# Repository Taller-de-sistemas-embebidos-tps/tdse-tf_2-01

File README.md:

# Sistema de detección de apneas y variaciones de oxigenación durante el sueño
<div align="center">

Trabajo Final - Taller de Sistemas Embebidos - FIUBA

|Alumno|Padron|
|------|-------|
|Tomás Musso Carboni|111548|
|Santiago Archetti|110707|
|Alan Romero|108316|
</div>

### Entrega
Se establece el plazo para entregar el proyecto finalizado para el periodo febrero-marzo.

## 1.1 Justificación de la elección del proyecto
Este proyecto se eligió porque los problemas respiratorios durante el sueño, como la apnea<sup>[1]</sup>, son muy comunes y muchas veces no se detectan a tiempo. La falta de diagnóstico puede generar cansancio crónico, bajo rendimiento y riesgos cardiovasculares, pero los estudios clínicos tradicionales suelen ser costosos y difíciles de realizar en el hogar. Por eso, un dispositivo portátil que mida la respiración y la saturación de oxígeno durante la noche resulta una herramienta útil y accesible para identificar posibles alteraciones.
Desde el punto de vista tecnológico, el proyecto es adecuado para el área de sistemas embebidos porque integra sensores reales, procesamiento digital, comunicación inalámbrica y manejo de bajo consumo. Además, el hardware seleccionado (MAX30102 y STM32F103RB) es económico, fácil de conseguir y cuenta con buena documentación, lo que facilita el desarrollo y permite enfocarse en el funcionamiento del sistema sin una complejidad excesiva. En conjunto, esto hace que el proyecto sea realizable, educativo y al mismo tiempo relevante desde lo biomédico.
Para la elección del proyecto, se realiza un análisis profundo de los distintos criterios que lo componen, asignando un peso a cada uno de ellos para luego hacer un análisis total.
|Criterio|Descripción|Puntuación|Peso final|
|----------|-------------|------------|------------|
|Tiempo y facilidad de implementación. Peso (7) |El uso del sensor MAX30102 y el microcontrolador STM32F103RB presenta una complejidad moderada, debido a la necesidad de configurar correctamente la comunicación I²C, filtrar la señal PPG y aplicar algoritmos de cálculo de SpO₂ y frecuencia respiratoria. Sin embargo, existe amplia documentación y librerías disponibles, lo que reduce las dificultades de implementación. En conjunto, se considera que la complejidad técnica es manejable dentro del marco de un proyecto de sistemas embebidos.| <p align="center">7</p> | 49 |
|Disponibilidad y costo de hardware. Peso (8) | Los componentes principales —sensor óptico MAX30102, microcontrolador STM32, módulo Bluetooth y un buzzer/LED para alarmas— son económicos, fáciles de conseguir y ampliamente utilizados en proyectos biomédicos educativos. Esto permite realizar pruebas sin un costo elevado y garantiza buena disponibilidad de reemplazos. |<p align="center">9</p>|72|
|Facilidad de realización de pruebas. Peso (5)|La verificación del funcionamiento del sistema puede realizarse mediante lectura directa de las señales PPG, monitoreo en tiempo real por UART/Bluetooth y observación de la activación de alarmas locales. Además, se pueden usar herramientas básicas como un multímetro o un osciloscopio para validar etapas eléctricas, lo que facilita enormemente el proceso de pruebas y depuración.| <p align="center">7</p>| 35 |
|Utilidad e interés personal en el proyecto. Peso (9)| El proyecto presenta un alto interés personal debido a su relación con aplicaciones biomédicas reales, la posibilidad de detectar apneas y desaturaciones durante el sueño, y su potencial mejora en versiones futuras. Además, permite aplicar conocimientos de sensores ópticos, filtrado digital y diseño embebido, lo que resulta atractivo tanto desde el punto de vista académico como práctico.|<p align="center"> 9</p>| 81 |

<p align="center"><b>Tabla 1: Evaluación de criterios del proyecto</b></p>

## 2.1 Objetivo del Proyecto
Diseñar y desarrollar un dispositivo portátil no invasivo capaz de medir en tiempo real la saturación de oxígeno (SpO₂) y la frecuencia respiratoria mediante técnicas de fotopletismografía. El objetivo es obtener señales fisiológicas confiables, procesarlas de forma local a través del microcontrolador STM32F103RB y generar alertas inmediatas ante condiciones anómalas, garantizando un monitoreo continuo y seguro

## 2.2 Propósito del Proyecto
El propósito es brindar una herramienta accesible y de bajo consumo para el seguimiento básico de parámetros respiratorios y de oxigenación, destinada a aplicaciones clínicas simples, monitoreo domiciliario y apoyo en la detección temprana de eventos como apnea o desaturación. Se busca complementar el trabajo de profesionales de la salud y ofrecer al usuario información clara y oportuna sobre su estado fisiológico.

## 2.3 Alcance del Proyecto
El proyecto abarca el diseño electrónico, la implementación del firmware y el procesamiento digital de la señal proveniente del sensor MAX30102 para la obtención de SpO₂ y frecuencia respiratoria. Incluye la integración de alarmas locales (buzzer/LED) configuradas por umbrales, así como la transmisión inalámbrica de datos mediante Bluetooth hacia una aplicación móvil. El alcance no contempla funciones diagnósticas avanzadas ni interpretación médica, limitándose al monitoreo y notificación de parámetros básicos.
Se establece la primer mesa de feberero como fecha para finalizar el proyecto.

## 3.1 Arquitectura del sistema
El diseño se estructura en cuatro bloques funcionales: 
1.	Adquisición: captura de la señal de flujo sanguíneo del dedo<sup>[2]</sup> del paciente mediante fotodiodos y LEDs (Rojo/IR). 
2.	Procesamiento: filtrado digital y cálculo de algoritmos en el microcontrolador. 
3.	Interfaz: indicadores visuales y sonoros para el usuario. 
4.	Comunicación: transmisión inalámbrica de telemetría y almacenamiento de parámetros. 

## 3.2 Diseño de Hardware
-	Sensor MAX30102: módulo integrado de oximetría y ritmo cardíaco. Se comunica vía I²C y opera a 3,3V. Provee las lecturas crudas de absorción de luz roja e infrarroja necesarias para calcular la saturación y derivar la respiración. 
-	Microcontrolador STM32F103RB: seleccionado por su núcleo ARM Cortex-M4F (con unidad de punto flotante), esencial para ejecutar filtros digitales eficientes. Gestiona los buses I²C (sensor, EEPROM) y UART (Bluetooth). 
-	Módulo Bluetooth HM-10: interfaz UART transparente para enviar datos seriales a dispositivos móviles (Smartphone/PC). 
-	Almacenamiento: memoria EEPROM externa (serie 24C0x) para guardar configuraciones de usuario, como umbrales de alarma o logs de eventos. 
-	Gestión de Energía: alimentación mediante batería Li-ion con regulación LDO a 3,3V. Implementa modos de bajo consumo (STOP) durante la inactividad. 

## 3.3 Procesamiento de la señal
El firmware, desarrollado en C con librerías HAL, ejecuta el siguiente flujo cíclico: 
1.	Adquisición de Datos: lectura de la FIFO del MAX30102 para obtener muestras de los canales Rojo e Infrarrojo (IR). 
2.	Pre-procesamiento: aplicación de un filtro para eliminar el componente de continua (DC) y ruido de alta frecuencia.<sup>[3]</sup> 
3.	Cálculo de SpO₂: se basa en la relación de ratios ($R$) entre las componentes AC y DC de ambas longitudes de onda<sup>[4]</sup>:
    
$$ R = \frac{AC_{red}\cdot AC_{ir}}{DC_{red} \cdot Dc_{ir}} $$

$$ SpO_2 = 110 - 25 \cdot R $$

4.	Estimación de Frecuencia Respiratoria: se realiza mediante el análisis de la variabilidad de la línea base o la modulación de amplitud (envolvente) de la señal PPG, extrayendo componentes de baja frecuencia (0,2 – 0,3 Hz). 
5.	Lógica de Control: si el SpO₂ cae por debajo del 90%, o si hay variaciones de la freuencia respiratoria, se activa el led indicador. Si se detecta apena se activa la alarma. Finalmente, se empaquetan los datos y se envían por UART. 

# 4.1 Requerimientos funcionales

| Grupo  | ID   | Requerimiento Funcional    | Descripción                                                                   |
|---|------|-----------------------------|-------------------------------------------------------------------------------|
|Adquisición | 1.1  | Adquisición de señales     | Capturar señales ópticas Rojo/IR del MAX30102 vía I²C.                        |
|   | 1.2  | Lectura periódica          | Obtener muestras desde la FIFO del sensor.                                    |
|   | 1.3  | Análisis de variación      | Detectar variaciones necesarias para SpO₂ y respiración.                      |
| Procesamiento  | 2.1  | Filtrado digital           | Aplicar filtrado.                                                             |
|   | 2.2  | Cálculo de SpO₂            | Calcular SpO₂ mediante el ratio R (AC/DC Rojo y AC/DC IR).                    |
|   | 2.3  | Cálculo de respiración     | Estimar frecuencia respiratoria mediante análisis de envolvente o línea base. |
|   | 2.4  | Empaquetado de datos       | Generar paquete con SpO₂, respiración y estado.                               |
|  Indicadores | 3.1  | Alarma crítica             | Activar alarma sonora cuando se detecta apnea.                                   |
|   | 3.2  | Indicadores LED            | Mostrar estados (crítico, normal, error) mediante LEDs.                       |
|  Comunicación | 4.1  | Comunicación Bluetooth     | Transmitir datos vía HM-10 por UART.                                          |
|   | 4.2  | Envío de parámetros        | Enviar SpO₂, respiraciones y estado del paciente a la app.                    |
|   | 4.3  | Registro de eventos        | Informar alarmas, desconexiones o estados especiales.                         |
|   | 4.4  | Recepción de configuración | Recibir umbrales y parámetros desde la aplicación.                            |
|  Memoria | 5.1  | Guardar configuración      | Almacenar umbrales y parámetros en EEPROM.                                    |
|   | 5.2  | Restaurar valores          | Recuperar valores predeterminados si hay error de memoria.                    |
| Alimentación  | 6.1  | Alimentación               | Funcionamiento con batería Li-Ion y regulación a 3.3V.                        |
|   | 6.2  | Bajo consumo               | Entrar en modo STOP cuando no hay actividad.                                  |
|   | 6.3  | Reactivación               | Retomar actividad ante movimiento o comando.                                  |
<p align="center"><b>Tabla 2: Requerimentos funcionales</b></p>

## 4.2 Diagrama de bloques
En la siguiente figura se dennota el diagrama de bloques funcional del proyecto.

<div align="center">
  
  <p><b>Figura 1. Diagrama de bloques</b></p>
</div>

## 5.1 Modos de uso

| **Modo** | **Descripción** | **Cotas / Umbrales** | **Comportamiento Especial** |
|---------|-----------------|----------------------|------------------------------|
| **Adulto** | Modo estándar para usuarios adultos. Utiliza configuraciones típicas de umbral para SpO₂ y respiración. | • SpO₂ crítico: < **90%**  <br>• Frecuencia respiratoria: rangos normales adulto | • Activa alarmas ante valores críticos. <br>• Envío de datos por Bluetooth. |
| **Niño** | Modo adaptado para usuarios pediátricos, con umbrales más sensibles. | • SpO₂ crítico: < **92–93%**  <br>• Frecuencia respiratoria: rangos normales niño | • Mayor sensibilidad a variaciones pequeñas. <br>• Alarmas ajustadas a parámetros pediátricos. |
| **Sleep (Bajo Consumo)** | Modo de ahorro energético para monitoreo prolongado nocturno. | • Mantiene umbrales según modo Adulto/Niño seleccionado. | • Reduce frecuencia de muestreo y procesamiento. <br>• **Si pasan más de 10 minutos sin lectura válida, el sistema se apaga automáticamente.** |
<p align="center"><b>Tabla 3: Modos de uso</b></p>

## Referencias
1. National Institutes of Health (NIH) – Sleep Apnea Fact Sheet. Disponible en https://www.nhlbi.nih.gov/health/sleep-apnea
2. Sally K. Longmore et al., “A Comparison of Reflective Photoplethysmography for Detection of Heart Rate, Blood Oxygen Saturation, and Respiration Rate at Various Anatomical Locations”, *Sensors*, vol. 19, no. 8, 1874, Apr. 2019. Disponible en: https://www.mdpi.com/1424-8220/19/8/1874
3.  Park J., Seok H. S., Kim S. S., & Shin H. (2022). *Photoplethysmogram Analysis and Applications: An Integrative Review*. Frontiers in Physiology, 12, Article 808451. doi:10.3389/fphys.2021.808451. Disponible en: https://www.ncbi.nlm.nih.gov/pmc/articles/PMC8920970/ 
4.  MAX30102 – Pulse Oximeter and Heart-Rate Sensor Datasheet. Maxim Integrated. https://datasheets.maximintegrated.com/en/ds/MAX30102.pdf

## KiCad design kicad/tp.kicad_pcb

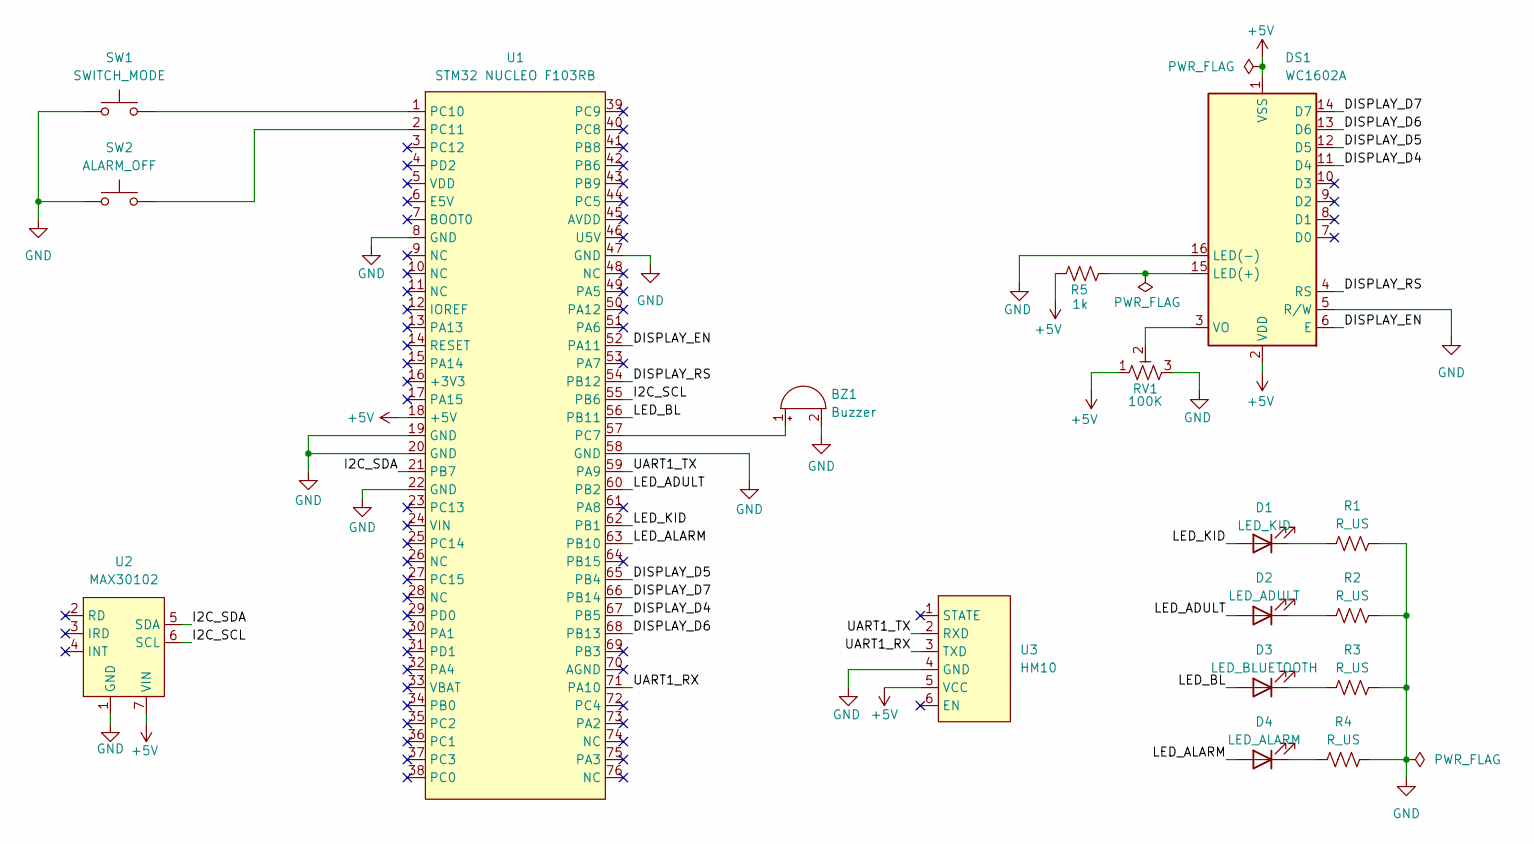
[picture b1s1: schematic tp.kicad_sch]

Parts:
BZ1: Buzzer; Buzzer_12x9.5RM7.6
D1: LED_KID; LED_D5.0mm
D2: LED_ADULT; LED_D5.0mm
D3: LED_BLUETOOTH; LED_D5.0mm
D4: LED_ALARM; LED_D5.0mm
DS1: WC1602A
R1, R2, R3, R4: R_US; R_Axial_DIN0207_L6.3mm_D2.5mm_P7.62mm_Horizontal
R5: 1k; R_Axial_DIN0207_L6.3mm_D2.5mm_P7.62mm_Horizontal
RV1: 100K; Potentiometer_Alps_RK163_Single_Horizontal
SW1: SWITCH_MODE; SW_PUSH-12mm_Wuerth-430476085716
SW2: ALARM_OFF; SW_PUSH-12mm_Wuerth-430476085716
U1: STM32 NUCLEO F103RB; NUCLEO F103RB
U2: MAX30102; PinHeader_1x07_P2.54mm_Vertical
U3: HM10; PinSocket_1x06_P2.54mm_Vertical

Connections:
+5V: DS1.1 (VSS), DS1.2 (VDD), R5.2, RV1.1, U1.18 (+5V), U2.7 (VIN), U3.5 (VCC)
/DISPLAY_D4: DS1.11 (D4), U1.67 (PB5)
/DISPLAY_D5: DS1.12 (D5), U1.65 (PB4)
/DISPLAY_D6: DS1.13 (D6), U1.68 (PB13)
/DISPLAY_D7: DS1.14 (D7), U1.66 (PB14)
/DISPLAY_EN: DS1.6 (E), U1.52 (PA11)
/DISPLAY_RS: DS1.4 (RS), U1.54 (PB12)
/I2C_SCL: U1.55 (PB6), U2.6 (SCL)
/I2C_SDA: U1.21 (PB7), U2.5 (SDA)
/LED_ADULT: D2.2 (A), U1.60 (PB2)
/LED_ALARM: D4.2 (A), U1.63 (PB10)
/LED_BL: D3.2 (A), U1.56 (PB11)
/LED_KID: D1.2 (A), U1.62 (PB1)
/UART1_RX: U1.71 (PA10), U3.3 (TXD)
/UART1_TX: U1.59 (PA9), U3.2 (RXD)
GND: BZ1.2 (-), DS1.5 (R/W), DS1.16 (LED(-)), R1.2, R2.2, R3.2, R4.2, RV1.3, SW1.1, SW2.1, U1.8 (GND), U1.19 (GND), U1.20 (GND), U1.22 (GND), U1.47 (GND), U1.58 (GND), U2.1 (GND), U3.4 (GND)
unnamed: BZ1.1 (+), U1.57 (PC7)
unnamed: D1.1 (K), R1.1
unnamed: D2.1 (K), R2.1
unnamed: D3.1 (K), R3.1
unnamed: D4.1 (K), R4.1
unnamed: DS1.15 (LED(+)), R5.1
unnamed: DS1.3 (VO), RV1.2
unnamed: SW1.2, U1.1 (PC10)
unnamed: SW2.2, U1.2 (PC11)

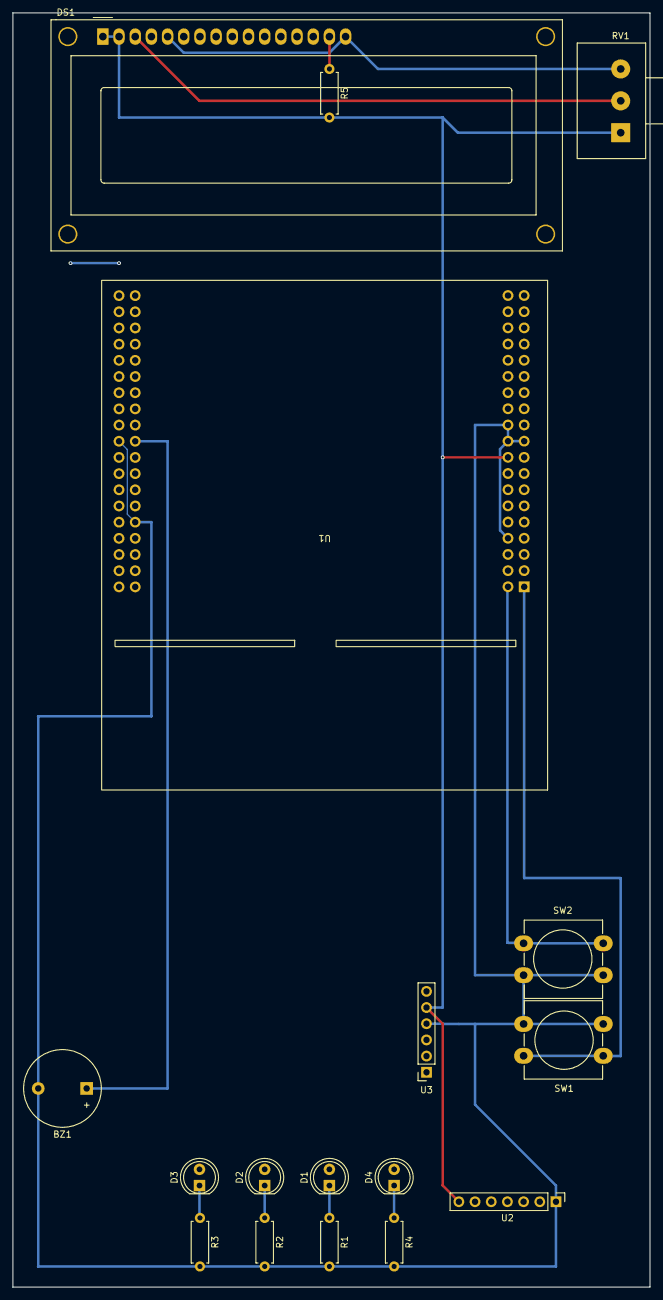
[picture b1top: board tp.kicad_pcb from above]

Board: 10 copper layers, 100.0 x 200.0 mm, 17 parts (0 on the bottom side), 25 nets.

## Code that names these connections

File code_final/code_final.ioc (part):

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Mcu.Name=STM32F103R(8-B)Tx
Mcu.Package=LQFP64
Mcu.UserName=STM32F103RBTx
PA10.Mode=Asynchronous
PA10.Signal=USART1_RX
PA11.GPIOParameters=GPIO_Label
PA11.GPIO_Label=DISPLAY_EN
PA11.Signal=GPIO_Output
PA13.GPIOParameters=GPIO_Label
PA13.GPIO_Label=TMS
PA13.Mode=Serial_Wire
PA13.Signal=SYS_JTMS-SWDIO
PA14.GPIOParameters=GPIO_Label
PA14.GPIO_Label=TCK
PA14.Mode=Serial_Wire
PA14.Signal=SYS_JTCK-SWCLK
PA2.GPIOParameters=GPIO_Speed,GPIO_PuPd,GPIO_Label,GPIO_Mode
PA2.GPIO_Label=USART_TX
PA2.GPIO_Mode=GPIO_MODE_AF_PP
PA2.GPIO_PuPd=GPIO_NOPULL
PA2.GPIO_Speed=GPIO_SPEED_FREQ_LOW
PA2.Mode=Asynchronous
PA2.Signal=USART2_TX
PA3.GPIOParameters=GPIO_Speed,GPIO_PuPd,GPIO_Label,GPIO_Mode
PA3.GPIO_Label=USART_RX
PA3.GPIO_Mode=GPIO_MODE_AF_PP
PA3.GPIO_PuPd=GPIO_NOPULL
PA3.GPIO_Speed=GPIO_SPEED_FREQ_LOW
PA3.Mode=Asynchronous
PA3.Signal=USART2_RX
PA5.GPIOParameters=GPIO_Speed,GPIO_PuPd,GPIO_Label,GPIO_ModeDefaultOutputPP
PA5.GPIO_Label=LD2 [Green Led]
PA5.GPIO_ModeDefaultOutputPP=GPIO_MODE_OUTPUT_PP
PA5.GPIO_PuPd=GPIO_NOPULL
PA5.GPIO_Speed=GPIO_SPEED_FREQ_LOW
PA5.Signal=GPIO_Output
PA9.Mode=Asynchronous
PA9.Signal=USART1_TX
PB1.GPIOParameters=GPIO_Label
PB1.GPIO_Label=LED_KID
PB1.Signal=GPIO_Output
PB10.GPIOParameters=GPIO_Label
PB10.GPIO_Label=LED_ALARM
PB10.Signal=GPIO_Output
PB11.GPIOParameters=GPIO_Label
PB11.GPIO_Label=LED_BL
PB11.Signal=GPIO_Output
PB12.GPIOParameters=GPIO_Label
PB12.GPIO_Label=DISPLAY_RS
PB12.Signal=GPIO_Output
PB13.GPIOParameters=GPIO_Label
PB13.GPIO_Label=DISPLAY_D6
PB13.Signal=GPIO_Output
PB14.GPIOParameters=GPIO_Label
PB14.GPIO_Label=DISPLAY_D7
PB14.Signal=GPIO_Output
PB2.GPIOParameters=GPIO_Label
PB2.GPIO_Label=LED_ADULT
PB2.Signal=GPIO_Output
PB3.GPIOParameters=GPIO_Label
PB3.GPIO_Label=SWO
PB3.Signal=SYS_JTDO-TRACESWO
PB4.GPIOParameters=GPIO_Label
PB4.GPIO_Label=DISPLAY_D5
PB4.Signal=GPIO_Output
PB5.GPIOParameters=GPIO_Label
PB5.GPIO_Label=DISPLAY_D4
PB5.Signal=GPIO_Output
PB6.Mode=I2C
PB6.Signal=I2C1_SCL
PB7.Mode=I2C
PB7.Signal=I2C1_SDA
PC10.GPIOParameters=GPIO_PuPd,GPIO_Label
PC10.GPIO_Label=BTN_MODE
PC10.GPIO_PuPd=GPIO_PULLUP
PC10.Signal=GPIO_Input
PC11.GPIOParameters=GPIO_PuPd,GPIO_Label
PC11.GPIO_Label=BTN_ALARM
PC11.GPIO_PuPd=GPIO_PULLUP
PC11.Signal=GPIO_Input
PC12.GPIOParameters=GPIO_PuPd,GPIO_Label
PC12.GPIO_Label=BTN_PAIRING
PC12.GPIO_PuPd=GPIO_NOPULL
PC12.Signal=GPIO_Input
PC13-TAMPER-RTC.GPIOParameters=GPIO_PuPd,GPIO_Label
PC13-TAMPER-RTC.GPIO_Label=B1 [Blue PushButton]
PC13-TAMPER-RTC.GPIO_PuPd=GPIO_NOPULL
PC13-TAMPER-RTC.Signal=GPXTI13
PC14-OSC32_IN.Mode=LSE-External-Oscillator
PC14-OSC32_IN.Signal=RCC_OSC32_IN
PC15-OSC32_OUT.Mode=LSE-External-Oscillator
PC15-OSC32_OUT.Signal=RCC_OSC32_OUT
PC7.GPIOParameters=GPIO_Label
PC7.GPIO_Label=BUZZER
PC7.Signal=GPIO_Output
PD0-OSC_IN.Mode=HSE-External-Clock-Source
PD0-OSC_IN.Signal=RCC_OSC_IN
PD1-OSC_OUT.Mode=HSE-External-Clock-Source
PD1-OSC_OUT.Signal=RCC_OSC_OUT
RCC.SYSCLKFreq_VALUE=64000000
RCC.SYSCLKSource=RCC_SYSCLKSOURCE_PLLCLK
board=NUCLEO-F103RB

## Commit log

2025-11-14 docs: Agrego periodo de entrega
2025-11-15 Primera version del readme, falta aun agregar contenido
2025-11-15 Adjunto diagrame de bloques
2025-11-15 docs: Arreglo URL del diagrama de bloques
2025-11-15 docs: Corrijo modelo de placa
2025-11-15 Correcion de imagenes y redaccón
2025-11-15 docs: Agrego padron
2025-11-19 Limpio el repositorio
2025-11-19 docs: agrego la descripción del proyecto
2025-11-20 docs: typo en ecuaciones
2025-11-22 docs: corrijo capitalización y formato en README
2025-12-07 feat(system): agrega diagrama de estados
2025-12-07 feat(system): agrega variables para la alarma
2025-12-07 feat(system_statechart): agrega estado compuesto para simplificar logica
2025-12-07 feat(system_statechart): se lanza evento para guardar datos desde el actuador
2025-12-07 fix(sys_statechart): nombre del archivo
2025-12-07 feat(sys_statechart): eleva eventos de alarma para el actuador
2025-12-07 fix(sys_statechart): se recuerda el ultimo modo elegido
2026-02-01 feat: agrega codigo base de proyecto
2026-02-02 feat: agrega botones de interaccion
2026-02-02 fix: comento pines no usados y arreglo las cfg de los botones
2026-02-05 Create Informe de avance
2026-02-05 typo
2026-02-05 docs: agrega bullet de alimentacion
2026-02-24 Implementación tareas de aplicación (sensor, actuator, comm, system)
2026-02-24 Actualización del Core STM32
2026-02-24 Resto de archivos del ide
2026-02-24 feat:agrega configuracion de pines del display al .ioc
2026-02-24 feat: descomenta el funcionamiento de los pines de display
2026-02-24 feat: reemplaza menú por system
2026-02-24 style: uppercase
2026-02-24 feat: agrega task_actuator
2026-02-24 feat: add foo test
2026-02-25 feat: agrega pines del display
2026-02-25 feat: descomenta uso de pines para display
2026-02-25 fix: typo y agrega boton de pairing
2026-02-25 feat: agrega esqueleto de tarea de comunicacion
2026-02-25 feat(comm): agrega estructuras de cfg y dta pertinentes
2026-02-25 refactor: comenta temporalmente la communicacion
    hasta saber bien como inicializar uart
2026-02-25 feat(actuator): actualiza cfg y dta por modelo real de un led/buzzer
2026-02-25 feat: agrega parámetro de futura optimización
2026-02-25 feat: actualiza interfaz para interactuar con el actuador
2026-02-25 feat(system): agrega system básico
2026-02-25 feat(button): agrega config pull_up de pines
2026-02-25 feat: agrega version de proyecto funcional
    el otro no corre los ticks y no sabemos por qué
2026-02-25 feat(button): cambio de pines a los nuestros
2026-02-25 refactor(system): attributes del system
2026-02-25 feat(actuator): agrega pines y attributos
2026-02-26 feat(system): solo ejecuta el statechart si hay eventos
2026-02-26 fix(actuator): agrega parametros de modo
2026-02-26 feat(system): agrega display lcd
2026-02-26 feat(actuator): agrega blink_funcional
2026-02-26 feat(system): se postea el evento blink al led bluetooth
2026-02-26 feat(comm): agrega modulo hm10
2026-02-26 feat(comm): agrego init del modulo bluetooth
2026-02-26 feat(system): agrego init del modulo bluetooth y checkeo rapido
2026-02-26 feat(button): el boton de pairing sera reemplazado por pin STATE
2026-02-26 feat(system): agrega attributo tick en dta
2026-02-26 feat(system): agrega posteo de info al hm10
    TODO: checkear si el pin STATE esta en ON
2026-02-26 feat(system): agrega mensajes periodicamente al modulo_bluetooth
    TODO: setear tick a una constante
2026-02-27 feat(comm): agrego task_comm
2026-02-27 feat(sch): agrega esquematico inicial con leds
2026-02-27 feat(sch): agrega botones
2026-02-27 fix(sch): agrega flag de power para ERC
2026-02-27 feat(sch): agrega display lcd
2026-02-27 feat(sch): agrega pines del hm10
2026-02-27 feat(sch): agrega pines del max30102
2026-02-27 style(sch): acomoda ubicaciones en la hoja
2026-02-27 docs(sch): agrega un pdf del esquematico
2026-03-04 feat(system): el systema envia datos por uart al modulo
2026-03-04 Agregando la carpeta del sensor al repositorio
2026-03-04 refactor(button): cambio de nombre sensor por boton
    el sensor es el max30102 no los botones
2026-03-04 chore: reubico archivo movido
2026-03-04 feat(sensor): habilita I2C en el .ioc
2026-03-04 feat(sensor): agrega funciones para leer el max30102 y procesar sus datos
2026-03-04 Agrego procesamiento de la señal max30102
2026-03-04 Borro archivo creado por error
2026-03-05 feat(sensor): agrega esqueleto de task para el sensor
2026-03-05 feat(sensor): el sensor postea al sistema datos (dummy) cada x ticks
2026-03-05 feat(system): recibe data del sensor y la postea cuando es nueva
2026-03-05 feat(system): agrega funcion para formatear sensor data a lcd 16x2
2026-03-05 chore: elimino proyecto anterior
2026-03-05 chore: agrega lista de pequeños TODOs que van surgiendo
2026-03-05 feat(sch): agrega symbol, footprint, y model de la NUCLEO-F103RB
2026-03-05 fix(sch): actualizo campos del symbol de la nucleo
2026-03-05 feat(sensor): agrega lectura del sensor cada 100 ticks
    si se cambia ticks a mas de 200 empieza a fallar
    no entra a los otros tasks
2026-03-05 fix(sch): elimino error de ERC en el symbol de nucleo
2026-03-05 feat(sensor): el sensor solo mide si detecta un dedo
    crear estados intermedios para confirmar dedo dentro o fuera (simil
    debouncing)
2026-03-05 feat(system): el sistema prende la alarma si detecta baja spo2
2026-03-05 chore: agrega TODOs
2026-03-05 Agrego logica de umbrales en sistema
2026-03-05 Correciones de texto.
2026-03-05 Correción de logica de control.
2026-03-05 feat(sch): agrego symbol del hm10
2026-03-06 feat(system): agrega logica de seteo de parametros en el task_system
    para setear los parametros segun el id
2026-03-06 fix(system): inicializa los parametros del system
2026-03-06 feat(sch): agrega symbols y conexiones faltantes
2026-03-06 fix(sch): actualizo el simbolo de la nucleo
2026-03-06 Agrego estados losing y detecting
2026-03-06 fix(system): los parametros son constantes
2026-03-06 feat(sch): agrego las footprints de los componentes
2026-03-06 feat(sch): agrega symbol custom del max30102
2026-03-06 fix(sch): el symbol tenia asociada una huella incorrecta
2026-03-06 fix(sch): actualiza symbol del max30102
2026-03-06 style(sch): cambio el footprint por un pinsocket
2026-03-06 feat(sch): agrego pcb de laa perfboard
2026-03-06 feat(sch): agrego agujeritos de perfboard en preview 3D
2026-03-08 feat(pcb): agrego modelo para el potenciómetro
    la footprint del potenciometro parece ser un poco mas pequeña que el
    modelo. O tal vez el modelo es muy grande(?
    comprobar con calibre
2026-03-08 feat(pcb): agrego script para exportar svg
2026-03-10 feat(kicad): agrego script para exportar svg y renders 3D
2026-03-10 Alternativa mas precisa para detectar apneas
2026-03-12 Modificacion del ioc
2026-03-14 Elimino carpeta sensor de prueba
2026-03-14 feat: informe en latex
    lleno de archivos basura
    agregarlos al .gitignore
2026-03-14 docs: test markdown
2026-03-15 docs: testea tags html
2026-03-16 docs: update informe
    by @sarchetti-create
2026-03-16 Factor de uso y consumo
2026-03-16 Agrego capturas de console y compile
2026-03-16 Ajusto parametros del sensor
2026-03-16 Quito comentarios innecesarios
2026-03-16 Mejoro redaccion, ordeno figura, agrego capitulo 4, indices y videos
2026-03-16 Ajuste indice
2026-03-16 Agrego tabla
2026-03-17 Agrego referencias, conclusiones, ajusto imagenes y titulos.
2026-03-17 Reorganizo seccion firmware
2026-03-17 Cambio puntos por coma en expresiones numericas
2026-03-17 Agrego asbtract
2026-03-17 Agrego preambulo en seccion 1
2026-03-17 Agrego un unico punto que me faltaba
2026-03-17 docs: update firmware
2026-03-17 Ajusto items 5.2
2026-03-17 Corrijo problemas en indice
2026-03-17 Agrego modulo procesamiento
2026-03-17 Agrego indice de ecuaciones
2026-03-17 Agrego tildes
2026-03-17 Elimino restos .tex
2026-03-17 Renombro carpeta
2026-03-19 Correción de la primer entrega
2026-03-19 refactor(system): los datos ppg se reciben a través de un evento
2026-03-19 refactor(actuator): elimino warnings
    si se entra en el case default se espera que el evento cambie y no se
    hace ningun cambio
2026-03-19 refactor(actuator): elimino pulse y variables no usadas
2026-03-21 Correciones luego de 2da entrega
2026-03-21 Pequeña correción
